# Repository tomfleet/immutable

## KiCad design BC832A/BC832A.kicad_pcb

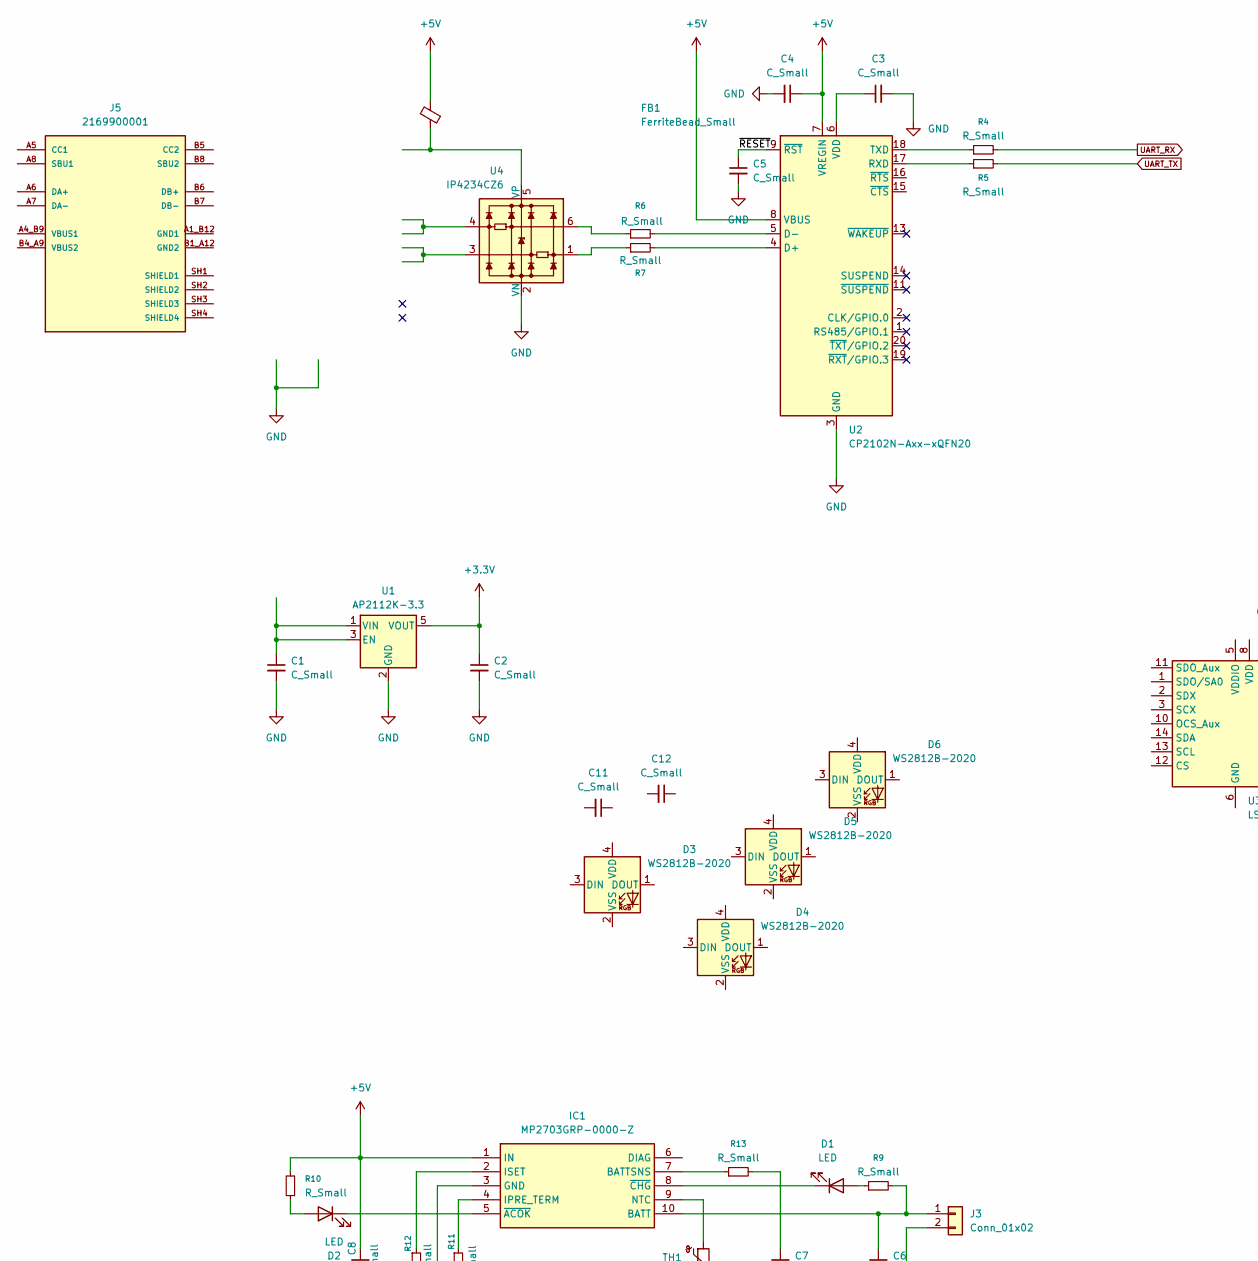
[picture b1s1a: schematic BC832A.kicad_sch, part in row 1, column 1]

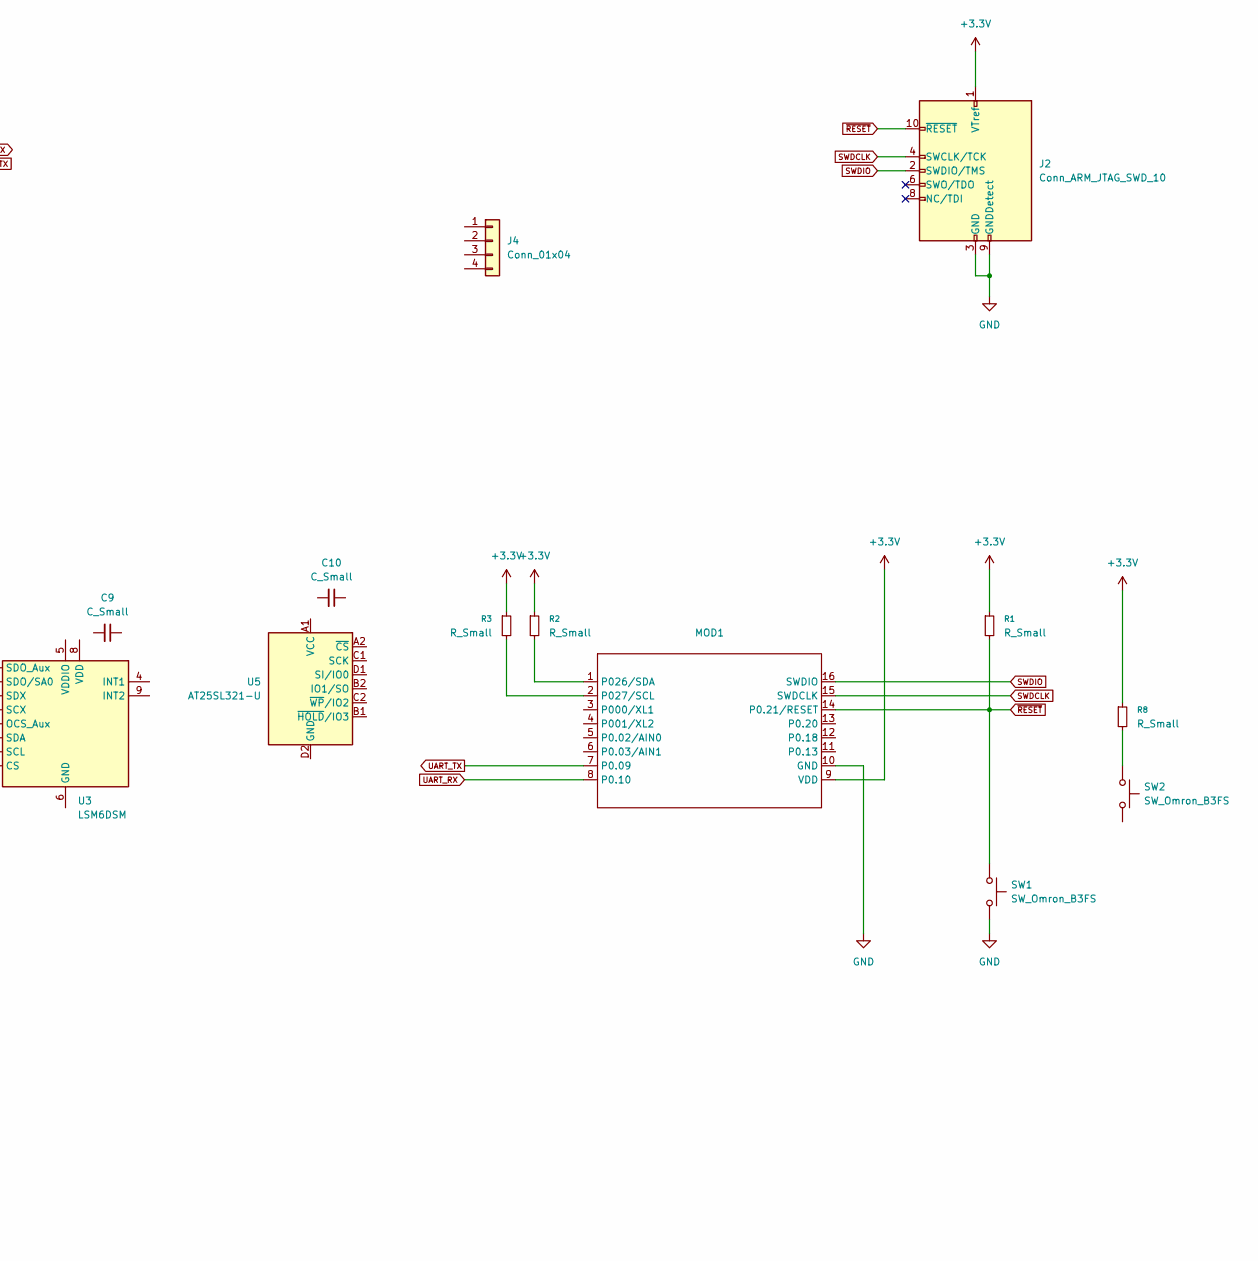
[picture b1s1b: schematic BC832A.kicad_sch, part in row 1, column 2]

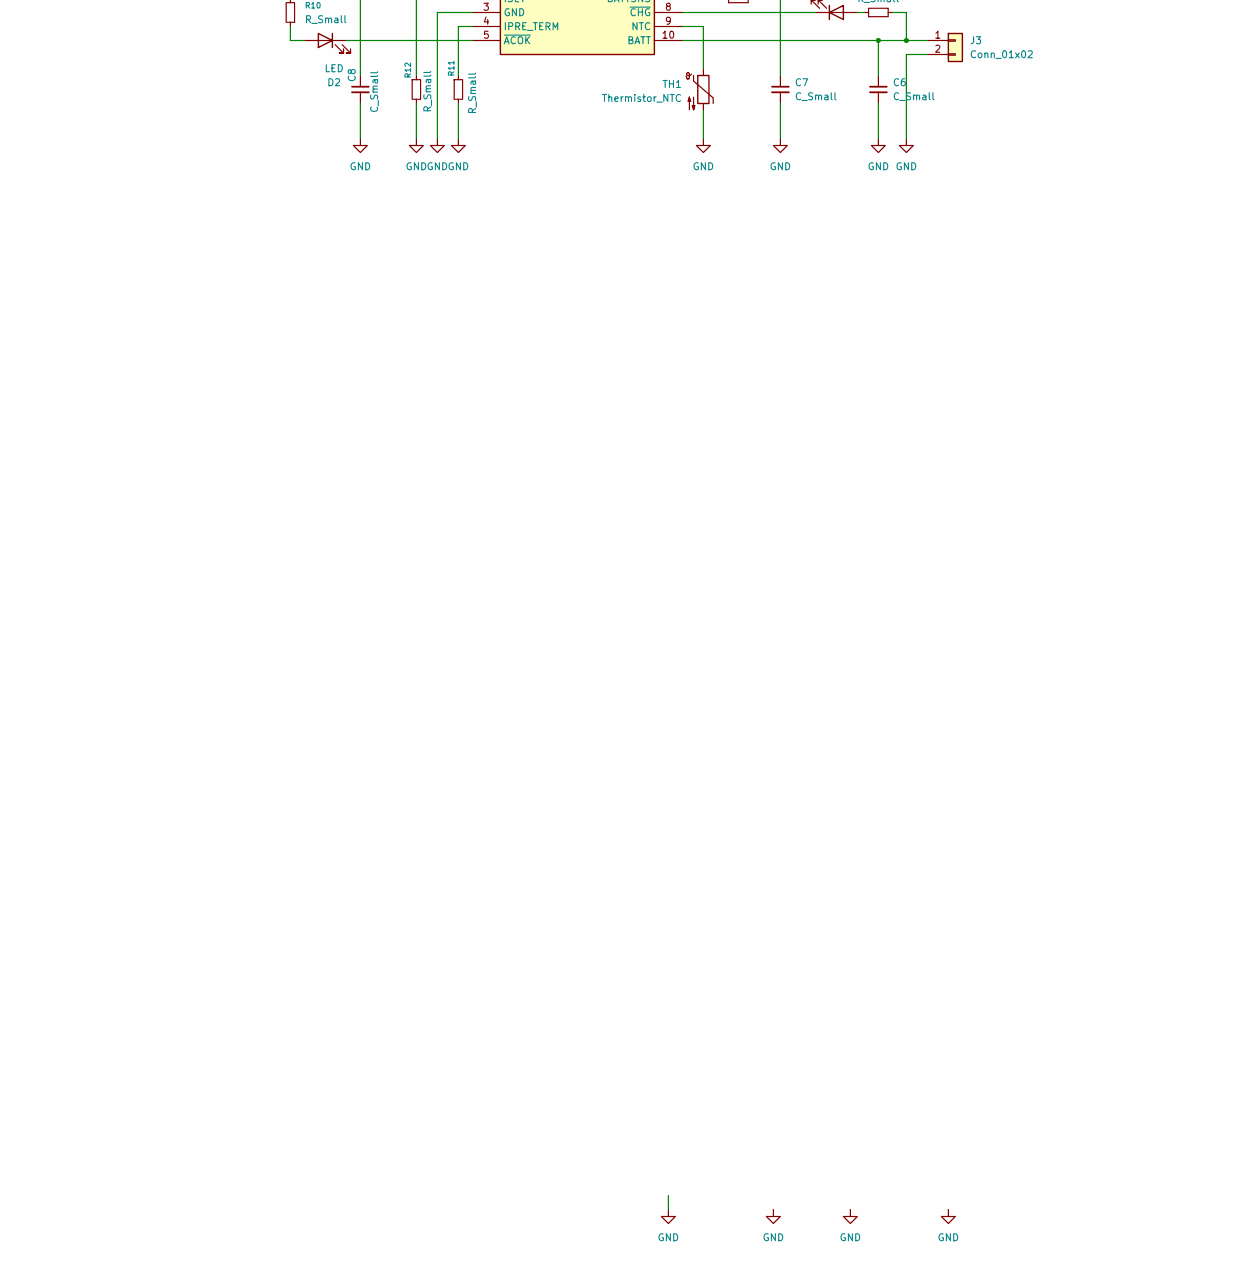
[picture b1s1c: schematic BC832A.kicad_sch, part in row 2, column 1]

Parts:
C1, C2, C3, C4, C5, C6, C7, C8, C9, C10, C11, C12: C_Small; C_0402_1005Metric
D1, D2: LED; LED_0402_1005Metric_Pad0.77x0.64mm_HandSolder
D3, D4, D5, D6: WS2812B-2020; LED_WS2812B-2020_PLCC4_2.0x2.0mm
FB1: FerriteBead_Small; L_0603_1608Metric_Pad1.05x0.95mm_HandSolder
IC1: MP2703GRP-0000-Z; MP2703GRP0000Z; Manufacturer_Part_Number MP2703GRP-0000-Z
J2: Conn_ARM_JTAG_SWD_10; PinHeader_2x05_P1.27mm_Vertical_SMD
J3: Conn_01x02; PinHeader_1x02_P1.27mm_Vertical
J4: Conn_01x04; Molex_Pico-Clasp_501331-0407_1x04-1MP_P1.00mm_Vertical
J5: 2169900001; MOLEX_2169900001; PARTREV A1; DigiKey_Part_Number 900-2169900001TR-ND
MOD1: bt832a_simple
R1, R2, R3, R4, R5, R6, R7, R8, R9, R10, R11, R12, R13: R_Small; R_0402_1005Metric_Pad0.72x0.64mm_HandSolder
SW1, SW2: SW_Omron_B3FS; SW_SPST_B3U-1000P
TH1: Thermistor_NTC
U1: AP2112K-3.3; SOT-23-5
U2: CP2102N-Axx-xQFN20; QFN-20-1EP_3x3mm_P0.4mm_EP1.65x1.65mm
U3: LSM6DSM; LGA-14_3x2.5mm_P0.5mm_LayoutBorder3x4y
U4: IP4234CZ6; SC-74-6_1.55x2.9mm_P0.95mm
U5: AT25SL321-U; WLCSP-8_1.551x2.284mm_Layout2x4_P0.5mm

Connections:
+3.3V: C2.1, J2.1 (VTref), MOD1.9 (VDD), R1.1, R2.1, R3.1, R8.1, U1.5 (VOUT)
+5V: C4.1, C8.1, FB1.2, IC1.1 (IN), R10.2, U2.7 (VREGIN), U2.8 (VBUS)
GND: C1.2, C2.2, C3.2, C4.2, C5.2, C6.2, C7.2, C8.2, IC1.3 (GND), J2.3 (GND), J2.5 (GND), J2.9 (GNDDetect), J3.2, MOD1.10 (GND), R11.2, R12.2, SW1.2, TH1.2, U1.2 (GND), U2.3 (GND), U2.12 (GND), U2.21 (GND), U4.2 (VN)
unnamed: C7.1, R13.2
unnamed: D1.2 (A), R9.1
unnamed: D1.1 (K), IC1.8 (~CHG)
unnamed: D2.2 (A), R10.1
unnamed: D2.1 (K), IC1.5 (~ACOK)
unnamed: C6.1, IC1.10 (BATT), J3.1, R9.2
unnamed: IC1.7 (BATTSNS), R13.1
unnamed: IC1.4 (IPRE_TERM), R11.1
unnamed: IC1.2 (ISET), R12.1
unnamed: IC1.9 (NTC), TH1.1
unnamed: MOD1.1 (P026/SDA), R2.2
unnamed: MOD1.2 (P027/SCL), R3.2
unnamed: R6.1, U4.6
unnamed: R7.1, U4.1
unnamed: R8.2, SW2.1
unnamed: C1.1, U1.1 (VIN), U1.3 (EN)
unnamed: R7.2, U2.4 (D+)
unnamed: R6.2, U2.5 (D-)
unnamed: R5.1, U2.17 (RXD)
unnamed: R4.1, U2.18 (TXD)
unnamed: C3.1, U2.6 (VDD)
unnamed: U3.6 (GND), U3.7 (GND)
unnamed: FB1.1, U4.5 (VP)
SWDCLK: J2.4 (SWCLK/TCK), MOD1.15 (SWDCLK)
SWDIO: J2.2 (SWDIO/TMS), MOD1.16 (SWDIO)
UART_RX: MOD1.8 (P0.10), R4.2
UART_TX: MOD1.7 (P0.09), R5.2
~RESET: C5.1, J2.10 (~RESET), MOD1.14 (P0.21/RESET), R1.2, SW1.1, U2.9 (~RST)

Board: 4 copper layers, 48 parts (1 on the bottom side), 31 nets, no tracks yet.

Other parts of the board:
C13, C14: C_Small; C_0402_1005Metric

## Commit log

2025-06-19 files
